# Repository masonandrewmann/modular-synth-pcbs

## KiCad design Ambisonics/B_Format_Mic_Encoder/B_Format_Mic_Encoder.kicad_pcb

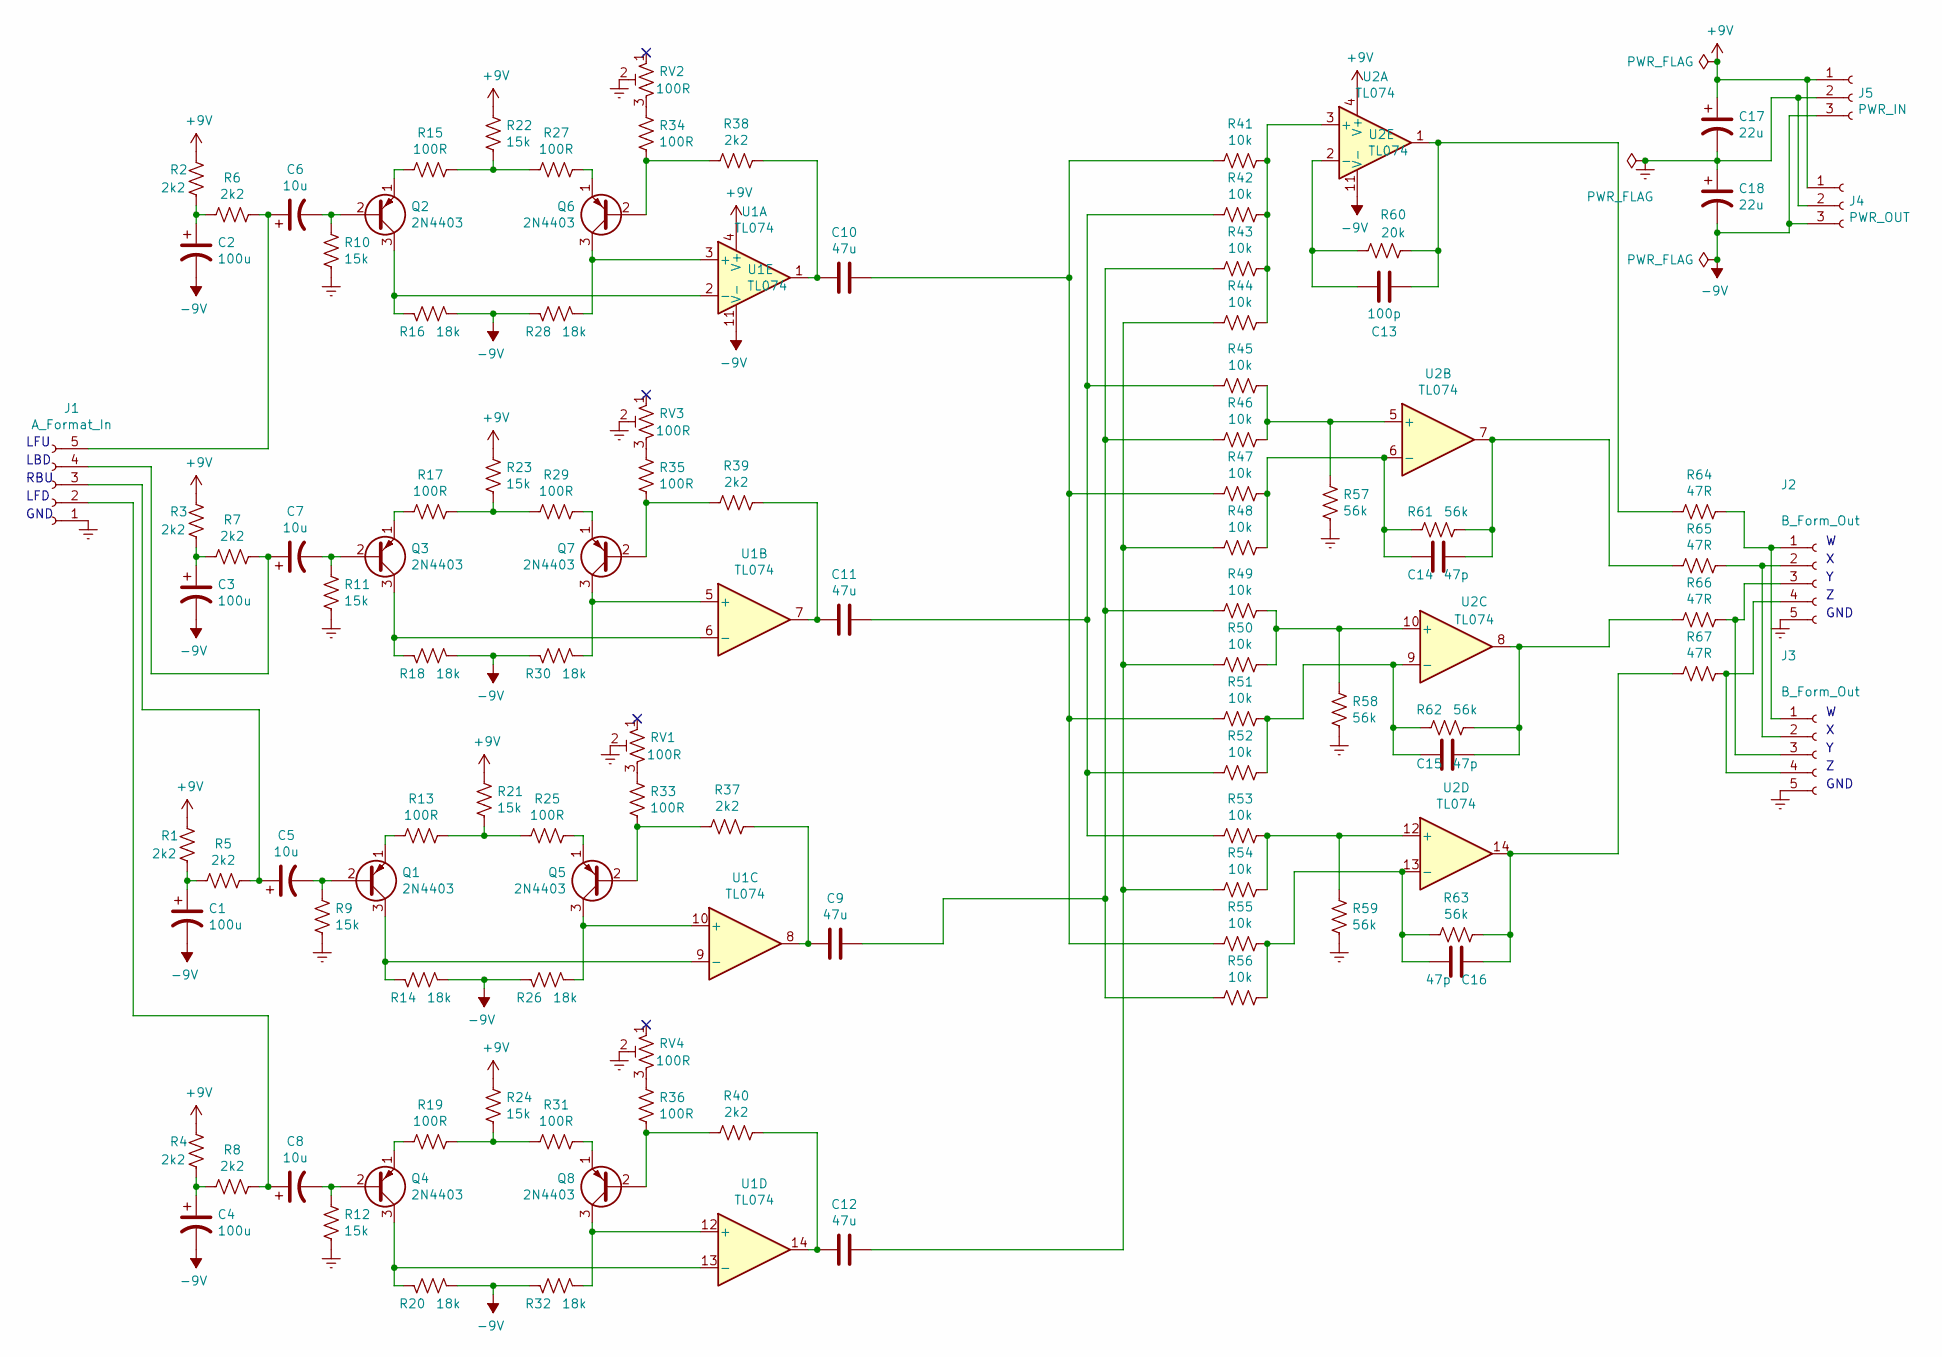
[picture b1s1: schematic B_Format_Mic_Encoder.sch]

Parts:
C1, C2, C3, C4: 100u; CP_Radial_D6.3mm_P2.50mm
C5, C6, C7, C8: 10u; CP_Radial_D6.3mm_P2.50mm
C9, C10, C11, C12: 47u; CP_Radial_D6.3mm_P2.50mm
C13: 100p; C_Rect_L7.0mm_W2.5mm_P5.00mm
C14, C15, C16: 47p; C_Rect_L7.0mm_W2.5mm_P5.00mm
C17, C18: 22u; CP_Radial_D6.3mm_P2.50mm
J1: A_Format_In; JST_XH_B5B-XH-A_1x05_P2.50mm_Vertical
J2, J3: B_Form_Out; JST_XH_B5B-XH-A_1x05_P2.50mm_Vertical
J4: PWR_OUT; JST_XH_B3B-XH-A_1x03_P2.50mm_Vertical
J5: PWR_IN; JST_XH_B3B-XH-A_1x03_P2.50mm_Vertical
Q1, Q2, Q3, Q4, Q5, Q6, Q7, Q8: 2N4403; TO-92L_Inline_Wide
R1, R2, R3, R4, R5, R6, R7, R8, R37, R38, R39, R40: 2k2; R_Axial_DIN0207_L6.3mm_D2.5mm_P7.62mm_Horizontal
R9, R10, R11, R12, R21, R22, R23, R24: 15k; R_Axial_DIN0207_L6.3mm_D2.5mm_P7.62mm_Horizontal
R13, R15, R17, R19, R25, R27, R29, R31, R33, R34, R35, R36: 100R; R_Axial_DIN0207_L6.3mm_D2.5mm_P7.62mm_Horizontal
R14, R16, R18, R20, R26, R28, R30, R32: 18k; R_Axial_DIN0207_L6.3mm_D2.5mm_P7.62mm_Horizontal
R41, R42, R43, R44, R45, R46, R47, R48, R49, R50, R51, R52, R53, R54, R55, R56: 10k; R_Axial_DIN0207_L6.3mm_D2.5mm_P7.62mm_Horizontal
R57, R58, R59, R61, R62, R63: 56k; R_Axial_DIN0207_L6.3mm_D2.5mm_P7.62mm_Horizontal
R60: 20k; R_Axial_DIN0207_L6.3mm_D2.5mm_P7.62mm_Horizontal
R64, R65, R66, R67: 47R; R_Axial_DIN0207_L6.3mm_D2.5mm_P7.62mm_Horizontal
RV1, RV2, RV3, RV4: 100R; Potentiometer_Runtron_RM-065_Vertical
U1, U2: TL074; DIP-14_W7.62mm_Socket

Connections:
+9V: C17.1, J4.1, J5.1, R1.2, R2.2, R3.2, R4.2, R21.2, R22.2, R23.2, R24.2, U1.4 (V+), U2.4 (V+)
-9V: C1.2, C2.2, C3.2, C4.2, C18.2, J4.3, J5.3, R14.1, R16.1, R18.1, R20.1, R26.2, R28.2, R30.2, R32.2, U1.11 (V-), U2.11 (V-)
Earth: C17.2, C18.1, J1.1, J2.5, J3.5, J4.2, J5.2, R9.2, R10.2, R11.2, R12.2, R57.1, R58.1, R59.1, RV1.2, RV2.2, RV3.2, RV4.2
unnamed: C1.1, R1.1, R5.2
unnamed: C2.1, R2.1, R6.2
unnamed: C3.1, R3.1, R7.2
unnamed: C4.1, R4.1, R8.2
unnamed: C5.1, J1.3, R5.1
unnamed: C5.2, Q1.2 (B), R9.1
unnamed: C6.1, J1.5, R6.1
unnamed: C6.2, Q2.2 (B), R10.1
unnamed: C7.1, J1.4, R7.1
unnamed: C7.2, Q3.2 (B), R11.1
unnamed: C8.1, J1.2, R8.1
unnamed: C8.2, Q4.2 (B), R12.1
unnamed: C9.1, R43.2, R46.2, R49.2, R56.2
unnamed: C9.2, R37.2, U1.8
unnamed: C10.1, R41.2, R47.2, R51.2, R55.2
unnamed: C10.2, R38.2, U1.1
unnamed: C11.1, R42.2, R45.2, R52.2, R53.2
unnamed: C11.2, R39.2, U1.7
unnamed: C12.1, R44.2, R48.2, R50.2, R54.2
unnamed: C12.2, R40.2, U1.14
unnamed: C13.1, R60.1, R64.1, U2.1
unnamed: C13.2, R60.2, U2.2 (-)
unnamed: C14.1, R61.1, R65.1, U2.7
unnamed: C14.2, R47.1, R48.1, R61.2, U2.6 (-)
unnamed: C15.1, R62.1, R66.1, U2.8
unnamed: C15.2, R51.1, R52.1, R62.2, U2.9 (-)
unnamed: C16.1, R63.1, R67.1, U2.14
unnamed: C16.2, R55.1, R56.1, R63.2, U2.13 (-)
unnamed: J2.1, J3.1, R64.2
unnamed: J2.2, J3.2, R65.2
unnamed: J2.3, J3.3, R66.2
unnamed: J2.4, J3.4, R67.2
unnamed: Q1.1 (E), R13.2
unnamed: Q1.3 (C), R14.2, U1.9 (-)
unnamed: Q2.1 (E), R15.2
unnamed: Q2.3 (C), R16.2, U1.2 (-)
unnamed: Q3.1 (E), R17.2
unnamed: Q3.3 (C), R18.2, U1.6 (-)
unnamed: Q4.1 (E), R19.2
unnamed: Q4.3 (C), R20.2, U1.13 (-)
unnamed: Q5.1 (E), R25.1
unnamed: Q5.2 (B), R33.1, R37.1
unnamed: Q5.3 (C), R26.1, U1.10 (+)
unnamed: Q6.1 (E), R27.1
unnamed: Q6.2 (B), R34.1, R38.1
unnamed: Q6.3 (C), R28.1, U1.3 (+)
unnamed: Q7.1 (E), R29.1
unnamed: Q7.2 (B), R35.1, R39.1
unnamed: Q7.3 (C), R30.1, U1.5 (+)
unnamed: Q8.1 (E), R31.1
unnamed: Q8.2 (B), R36.1, R40.1
unnamed: Q8.3 (C), R32.1, U1.12 (+)
unnamed: R13.1, R21.1, R25.2
unnamed: R15.1, R22.1, R27.2
unnamed: R17.1, R23.1, R29.2
unnamed: R19.1, R24.1, R31.2
unnamed: R33.2, RV1.3
unnamed: R34.2, RV2.3
unnamed: R35.2, RV3.3
unnamed: R36.2, RV4.3
unnamed: R41.1, R42.1, R43.1, R44.1, U2.3 (+)
unnamed: R45.1, R46.1, R57.2, U2.5 (+)
unnamed: R49.1, R50.1, R58.2, U2.10 (+)
unnamed: R53.1, R54.1, R59.2, U2.12 (+)

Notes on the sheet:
LFU
LBD
RBU
LFD
GND

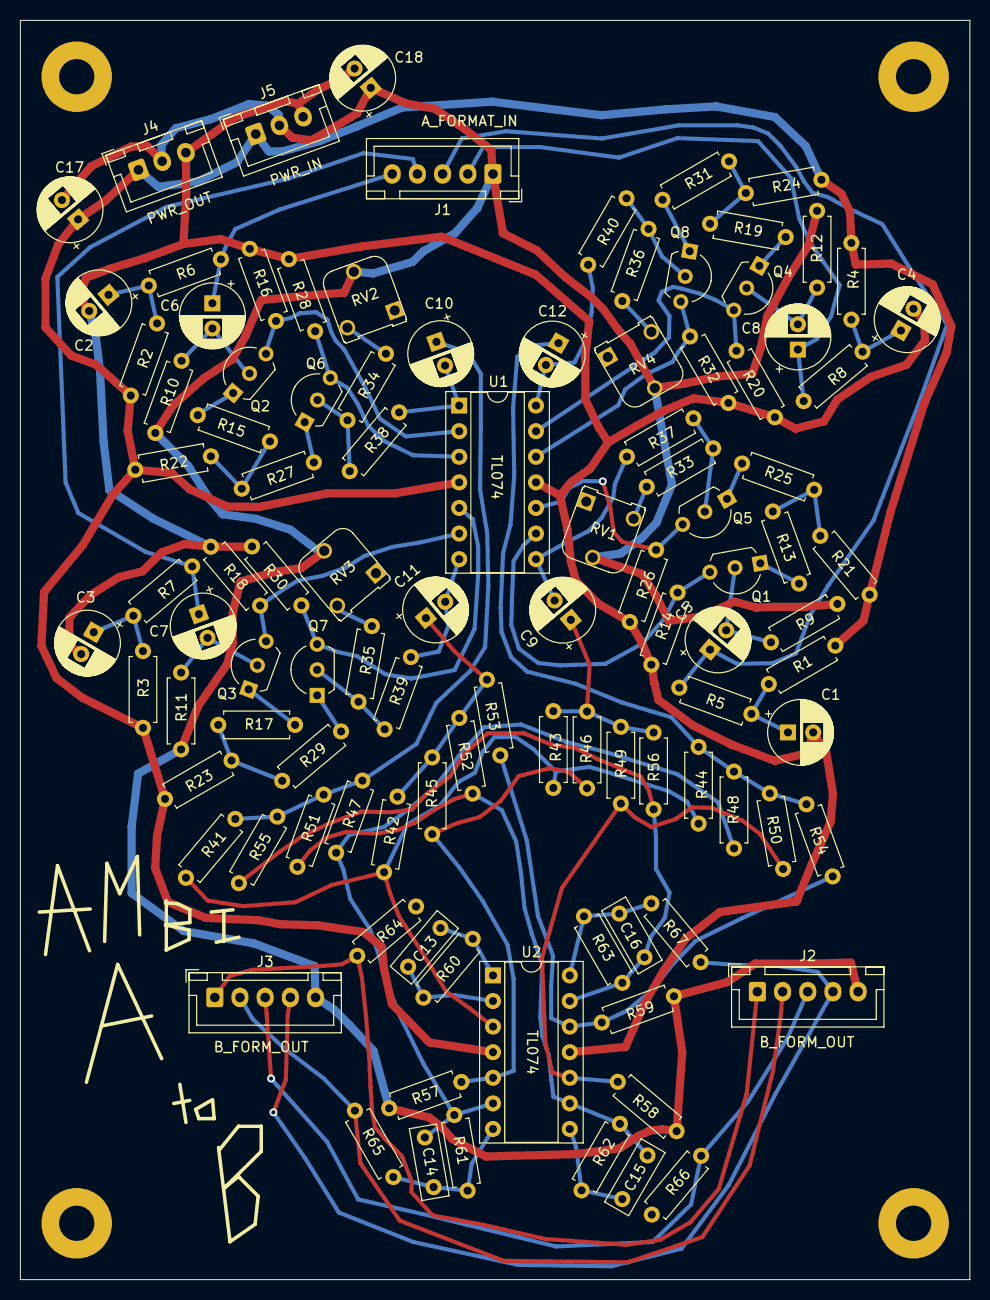
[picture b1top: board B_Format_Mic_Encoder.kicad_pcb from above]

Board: 2 copper layers, 94.2 x 125.0 mm, 104 parts (0 on the bottom side), 67 nets.

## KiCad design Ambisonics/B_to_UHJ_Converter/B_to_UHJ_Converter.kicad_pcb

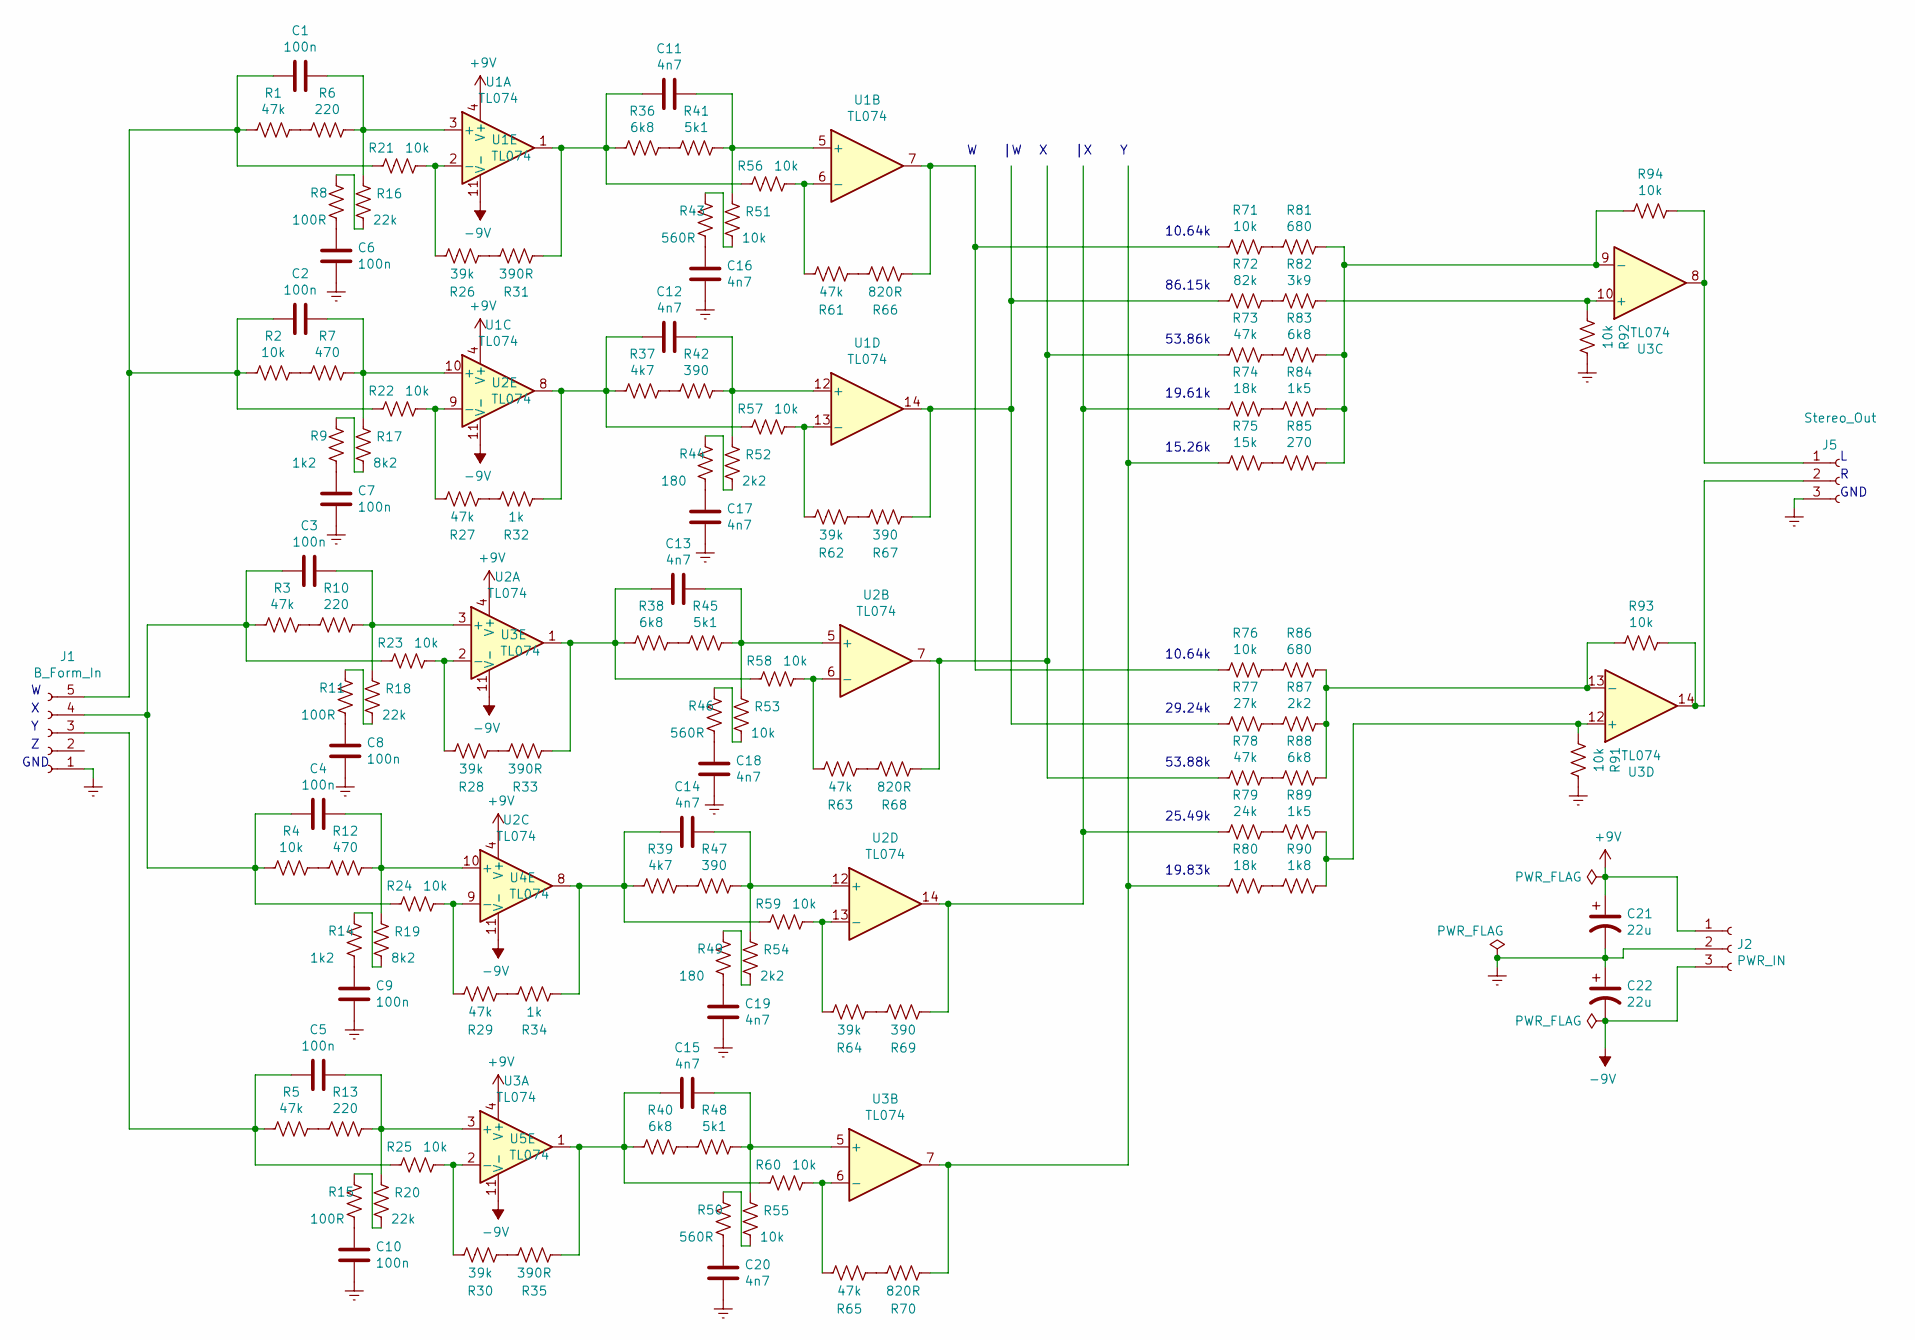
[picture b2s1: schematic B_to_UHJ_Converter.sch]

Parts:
C1, C2, C3, C4, C5, C6, C7, C8, C9, C10: 100n; C_Rect_L7.0mm_W2.5mm_P5.00mm
C11, C12, C13, C14, C15, C16, C17, C18, C19, C20: 4n7; C_Rect_L7.0mm_W2.5mm_P5.00mm
C21, C22: 22u; CP_Radial_D6.3mm_P2.50mm
J1: B_Form_In; JST_XH_B5B-XH-A_1x05_P2.50mm_Vertical
J2: PWR_IN; JST_XH_B3B-XH-A_1x03_P2.50mm_Vertical
J5: Stereo_Out; JST_XH_B3B-XH-A_1x03_P2.50mm_Vertical
R1, R3, R5, R27, R29, R61, R63, R65, R73, R78: 47k; R_Axial_DIN0207_L6.3mm_D2.5mm_P7.62mm_Horizontal
R2, R4, R21, R22, R23, R24, R25, R51, R53, R55, R56, R57, R58, R59, R60, R71, R76, R91, R92, R93, R94: 10k; R_Axial_DIN0207_L6.3mm_D2.5mm_P7.62mm_Horizontal
R6, R10, R13: 220; R_Axial_DIN0207_L6.3mm_D2.5mm_P7.62mm_Horizontal
R7, R12: 470; R_Axial_DIN0207_L6.3mm_D2.5mm_P7.62mm_Horizontal
R8, R11, R15: 100R; R_Axial_DIN0207_L6.3mm_D2.5mm_P7.62mm_Horizontal
R9, R14: 1k2; R_Axial_DIN0207_L6.3mm_D2.5mm_P7.62mm_Horizontal
R16, R18, R20: 22k; R_Axial_DIN0207_L6.3mm_D2.5mm_P7.62mm_Horizontal
R17, R19: 8k2; R_Axial_DIN0207_L6.3mm_D2.5mm_P7.62mm_Horizontal
R26, R28, R30, R62, R64: 39k; R_Axial_DIN0207_L6.3mm_D2.5mm_P7.62mm_Horizontal
R31, R33, R35: 390R; R_Axial_DIN0207_L6.3mm_D2.5mm_P7.62mm_Horizontal
R32, R34: 1k; R_Axial_DIN0207_L6.3mm_D2.5mm_P7.62mm_Horizontal
R36, R38, R40, R83, R88: 6k8; R_Axial_DIN0207_L6.3mm_D2.5mm_P7.62mm_Horizontal
R37, R39: 4k7; R_Axial_DIN0207_L6.3mm_D2.5mm_P7.62mm_Horizontal
R41, R45, R48: 5k1; R_Axial_DIN0207_L6.3mm_D2.5mm_P7.62mm_Horizontal
R42, R47, R67, R69: 390; R_Axial_DIN0207_L6.3mm_D2.5mm_P7.62mm_Horizontal
R43, R46, R50: 560R; R_Axial_DIN0207_L6.3mm_D2.5mm_P7.62mm_Horizontal
R44, R49: 180; R_Axial_DIN0207_L6.3mm_D2.5mm_P7.62mm_Horizontal
R52, R54, R87: 2k2; R_Axial_DIN0207_L6.3mm_D2.5mm_P7.62mm_Horizontal
R66, R68, R70: 820R; R_Axial_DIN0207_L6.3mm_D2.5mm_P7.62mm_Horizontal
R72: 82k; R_Axial_DIN0207_L6.3mm_D2.5mm_P7.62mm_Horizontal
R74, R80: 18k; R_Axial_DIN0207_L6.3mm_D2.5mm_P7.62mm_Horizontal
R75: 15k; R_Axial_DIN0207_L6.3mm_D2.5mm_P7.62mm_Horizontal
R77: 27k; R_Axial_DIN0207_L6.3mm_D2.5mm_P7.62mm_Horizontal
R79: 24k; R_Axial_DIN0207_L6.3mm_D2.5mm_P7.62mm_Horizontal
R81, R86: 680; R_Axial_DIN0207_L6.3mm_D2.5mm_P7.62mm_Horizontal
R82: 3k9; R_Axial_DIN0207_L6.3mm_D2.5mm_P7.62mm_Horizontal
R84, R89: 1k5; R_Axial_DIN0207_L6.3mm_D2.5mm_P7.62mm_Horizontal
R85: 270; R_Axial_DIN0207_L6.3mm_D2.5mm_P7.62mm_Horizontal
R90: 1k8; R_Axial_DIN0207_L6.3mm_D2.5mm_P7.62mm_Horizontal
U1, U2, U3, U4, U5: TL074; DIP-14_W7.62mm_Socket

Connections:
+9V: C21.1, J2.1, U1.4 (V+), U2.4 (V+), U3.4 (V+), U4.4 (V+), U5.4 (V+)
-9V: C22.2, J2.3, U1.11 (V-), U2.11 (V-), U3.11 (V-), U4.11 (V-), U5.11 (V-)
Earth: C6.1, C7.1, C8.1, C9.1, C10.1, C16.1, C17.1, C18.1, C19.1, C20.1, C21.2, C22.1, J1.1, J2.2, J5.3, R91.1, R92.1
unnamed: C1.1, R6.1, R16.2, U1.3 (+)
unnamed: C1.2, C2.2, J1.5, R1.2, R2.2, R21.2, R22.2
unnamed: C2.1, R7.1, R17.2, U1.10 (+)
unnamed: C3.1, R10.1, R18.2, U2.3 (+)
unnamed: C3.2, C4.2, J1.4, R3.2, R4.2, R23.2, R24.2
unnamed: C4.1, R12.1, R19.2, U2.10 (+)
unnamed: C5.1, R13.1, R20.2, U3.3 (+)
unnamed: C5.2, J1.3, R5.2, R25.2
unnamed: C6.2, R8.1
unnamed: C7.2, R9.1
unnamed: C8.2, R11.1
unnamed: C9.2, R14.1
unnamed: C10.2, R15.1
unnamed: C11.1, R41.1, R51.2, U1.5 (+)
unnamed: C11.2, R31.1, R36.2, R56.2, U1.1
unnamed: C12.1, R42.1, R52.2, U1.12 (+)
unnamed: C12.2, R32.1, R37.2, R57.2, U1.8
unnamed: C13.1, R45.1, R53.2, U2.5 (+)
unnamed: C13.2, R33.1, R38.2, R58.2, U2.1
unnamed: C14.1, R47.1, R54.2, U2.12 (+)
unnamed: C14.2, R34.1, R39.2, R59.2, U2.8
unnamed: C15.1, R48.1, R55.2, U3.5 (+)
unnamed: C15.2, R35.1, R40.2, R60.2, U3.1
unnamed: C16.2, R43.1
unnamed: C17.2, R44.1
unnamed: C18.2, R46.1
unnamed: C19.2, R49.1
unnamed: C20.2, R50.1
unnamed: J5.1, R94.1, U3.8
unnamed: J5.2, R93.1, U3.14
unnamed: R1.1, R6.2
unnamed: R2.1, R7.2
unnamed: R3.1, R10.2
unnamed: R11.2, R18.1
unnamed: R4.1, R12.2
unnamed: R5.1, R13.2
unnamed: R14.2, R19.1
unnamed: R15.2, R20.1
unnamed: R8.2, R16.1
unnamed: R9.2, R17.1
unnamed: R21.1, R26.2, U1.2 (-)
unnamed: R22.1, R27.2, U1.9 (-)
unnamed: R23.1, R28.2, U2.2 (-)
unnamed: R24.1, R29.2, U2.9 (-)
unnamed: R25.1, R30.2, U3.2 (-)
unnamed: R26.1, R31.2
unnamed: R27.1, R32.2
unnamed: R28.1, R33.2
unnamed: R29.1, R34.2
unnamed: R30.1, R35.2
unnamed: R36.1, R41.2
unnamed: R37.1, R42.2
unnamed: R38.1, R45.2
unnamed: R39.1, R47.2
unnamed: R40.1, R48.2
unnamed: R43.2, R51.1
unnamed: R44.2, R52.1
unnamed: R46.2, R53.1
unnamed: R49.2, R54.1
unnamed: R50.2, R55.1
unnamed: R56.1, R61.2, U1.6 (-)
unnamed: R57.1, R62.2, U1.13 (-)
unnamed: R58.1, R63.2, U2.6 (-)
unnamed: R59.1, R64.2, U2.13 (-)
unnamed: R60.1, R65.2, U3.6 (-)
unnamed: R61.1, R66.2
unnamed: R62.1, R67.2
unnamed: R63.1, R68.2
unnamed: R64.1, R69.2
unnamed: R65.1, R70.2
unnamed: R66.1, R71.2, R76.2, U1.7
unnamed: R67.1, R72.2, R77.2, U1.14
unnamed: R68.1, R73.2, R78.2, U2.7
unnamed: R69.1, R74.2, R79.2, U2.14
unnamed: R70.1, R75.2, R80.2, U3.7
unnamed: R71.1, R81.2
unnamed: R72.1, R82.2
unnamed: R73.1, R83.2
unnamed: R74.1, R84.2
unnamed: R75.1, R85.2
unnamed: R76.1, R86.2
unnamed: R77.1, R87.2
unnamed: R78.1, R88.2
unnamed: R79.1, R89.2
unnamed: R80.1, R90.2
unnamed: R81.1, R83.1, R84.1, R85.1, R94.2, U3.9 (-)
unnamed: R82.1, R92.2, U3.10 (+)
unnamed: R86.1, R87.1, R88.1, R93.2, U3.13 (-)
unnamed: R89.1, R90.1, R91.2, U3.12 (+)

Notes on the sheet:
10.64k
86.15k
53.86k
19.61k
15.26k
29.24k
53.88k
25.49k
19.83k
GND

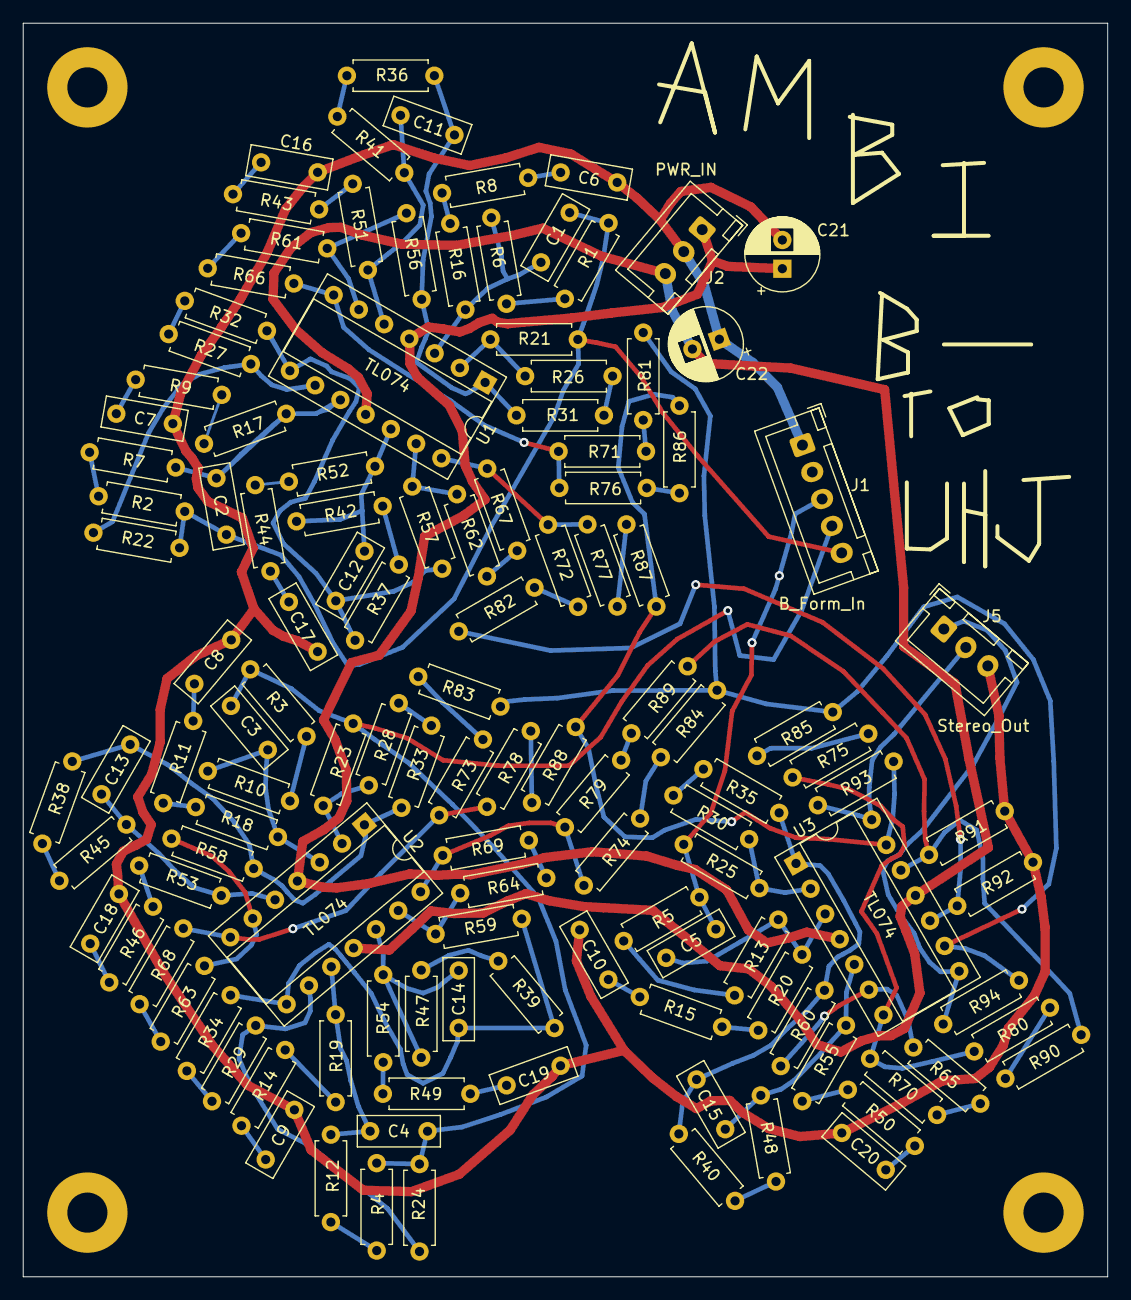
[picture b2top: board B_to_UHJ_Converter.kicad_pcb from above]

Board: 2 copper layers, 94.5 x 109.2 mm, 122 parts (0 on the bottom side), 92 nets.

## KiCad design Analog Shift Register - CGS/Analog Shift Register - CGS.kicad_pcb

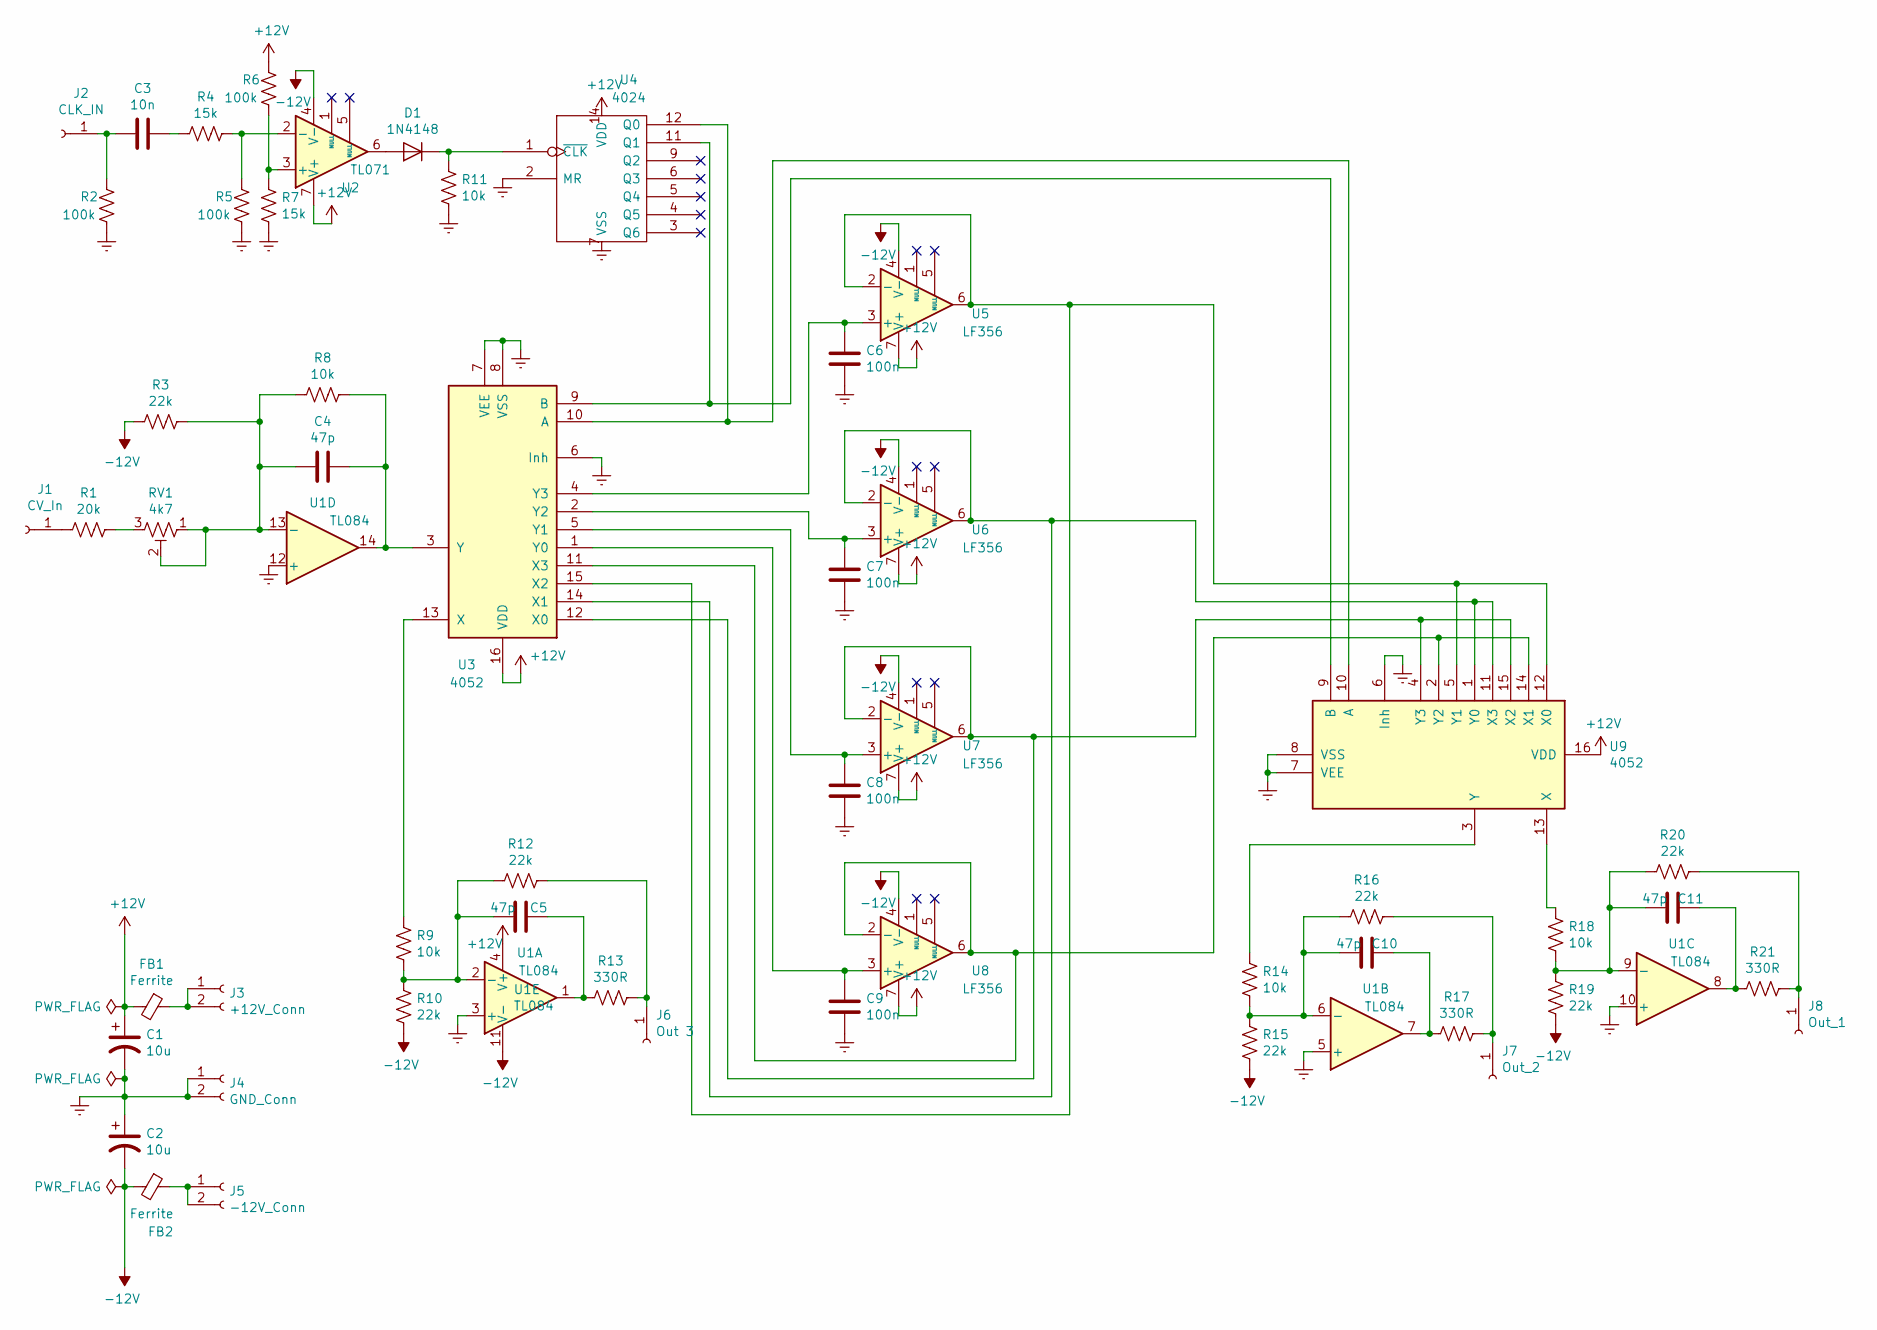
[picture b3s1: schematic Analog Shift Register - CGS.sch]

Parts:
C1, C2: 10u; CP_Radial_D4.0mm_P2.00mm
C3: 10n; C_Rect_L7.0mm_W2.5mm_P5.00mm
C4, C5, C10, C11: 47p; C_Rect_L7.0mm_W2.5mm_P5.00mm
C6, C7, C8, C9: 100n; C_Rect_L7.0mm_W2.5mm_P5.00mm
D1: 1N4148; D_T-1_P5.08mm_Horizontal
FB1, FB2: Ferrite; L_Axial_L7.0mm_D3.3mm_P10.16mm_Horizontal_Fastron_MICC
J1: CV_In; SolderWirePad_1x01_Drill1mm
J2: CLK_IN; SolderWirePad_1x01_Drill1mm
J3: +12V_Conn; SolderWirePad_1x02_P3.81mm_Drill1mm
J4: GND_Conn; SolderWirePad_1x02_P3.81mm_Drill1mm
J5: -12V_Conn; SolderWirePad_1x02_P3.81mm_Drill1mm
J6: Out 3; SolderWirePad_1x01_Drill1mm
J7: Out_2; SolderWirePad_1x01_Drill1mm
J8: Out_1; SolderWirePad_1x01_Drill1mm
R1: 20k; R_Axial_DIN0207_L6.3mm_D2.5mm_P7.62mm_Horizontal
R2, R5, R6: 100k; R_Axial_DIN0207_L6.3mm_D2.5mm_P7.62mm_Horizontal
R3, R10, R12, R15, R16, R19, R20: 22k; R_Axial_DIN0207_L6.3mm_D2.5mm_P7.62mm_Horizontal
R4, R7: 15k; R_Axial_DIN0207_L6.3mm_D2.5mm_P7.62mm_Horizontal
R8, R9, R11, R14, R18: 10k; R_Axial_DIN0207_L6.3mm_D2.5mm_P7.62mm_Horizontal
R13, R17, R21: 330R; R_Axial_DIN0207_L6.3mm_D2.5mm_P7.62mm_Horizontal
RV1: 4k7; Potentiometer_Runtron_RM-065_Vertical
U1: TL084; DIP-14_W7.62mm_Socket
U2: TL071; DIP-8_W7.62mm_Socket
U3, U9: 4052; DIP-16_W7.62mm_Socket
U4: 4024; DIP-14_W7.62mm_Socket
U5, U6, U7, U8: LF356; DIP-8_W7.62mm_Socket

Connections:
+12V: C1.1, FB1.2, R6.2, U1.4 (V+), U2.7 (V+), U3.16 (VDD), U4.14 (VDD), U5.7 (V+), U6.7 (V+), U7.7 (V+), U8.7 (V+), U9.16 (VDD)
-12V: C2.2, FB2.2, R3.2, R10.1, R15.1, R19.1, U1.11 (V-), U2.4 (V-), U5.4 (V-), U6.4 (V-), U7.4 (V-), U8.4 (V-)
Earth: C1.2, C2.1, C6.2, C7.2, C8.2, C9.2, J4.1, J4.2, R2.1, R5.1, R7.1, R11.1, U1.3 (+), U1.5 (+), U1.10 (+), U1.12 (+), U3.6 (Inh), U3.7 (VEE), U3.8 (VSS), U4.2 (MR), U4.7 (VSS), U9.6 (Inh), U9.7 (VEE), U9.8 (VSS)
unnamed: C3.1, R4.1
unnamed: C3.2, J2.1, R2.2
unnamed: C4.1, R8.1, U1.14, U3.3 (Y)
unnamed: C4.2, R3.1, R8.2, RV1.1, RV1.2, U1.13 (-)
unnamed: C5.1, R13.2, U1.1
unnamed: C5.2, R9.1, R10.2, R12.2, U1.2 (-)
unnamed: C6.1, U3.4 (Y3), U5.3 (+)
unnamed: C7.1, U3.2 (Y2), U6.3 (+)
unnamed: C8.1, U3.5 (Y1), U7.3 (+)
unnamed: C9.1, U3.1 (Y0), U8.3 (+)
unnamed: C10.1, R17.2, U1.7
unnamed: C10.2, R14.1, R15.2, R16.2, U1.6 (-)
unnamed: C11.1, R21.2, U1.8
unnamed: C11.2, R18.1, R19.2, R20.2, U1.9 (-)
unnamed: D1.1 (K), R11.2, U4.1 (~CLK)
unnamed: D1.2 (A), U2.6
unnamed: FB1.1, J3.1, J3.2
unnamed: FB2.1, J5.1, J5.2
unnamed: J1.1, R1.2
unnamed: J6.1, R12.1, R13.1
unnamed: J7.1, R16.1, R17.1
unnamed: J8.1, R20.1, R21.1
unnamed: R1.1, RV1.3
unnamed: R4.2, R5.2, U2.2 (-)
unnamed: R6.1, R7.2, U2.3 (+)
unnamed: R9.2, U3.13 (X)
unnamed: R14.2, U9.3 (Y)
unnamed: R18.2, U9.13 (X)
unnamed: U3.9 (B), U4.11 (Q1), U9.9 (B)
unnamed: U3.10 (A), U4.12 (Q0), U9.10 (A)
unnamed: U3.11 (X3), U8.2 (-), U8.6, U9.2 (Y2), U9.14 (X1)
unnamed: U3.12 (X0), U7.2 (-), U7.6, U9.4 (Y3), U9.15 (X2)
unnamed: U3.14 (X1), U6.2 (-), U6.6, U9.1 (Y0), U9.11 (X3)
unnamed: U3.15 (X2), U5.2 (-), U5.6, U9.5 (Y1), U9.12 (X0)

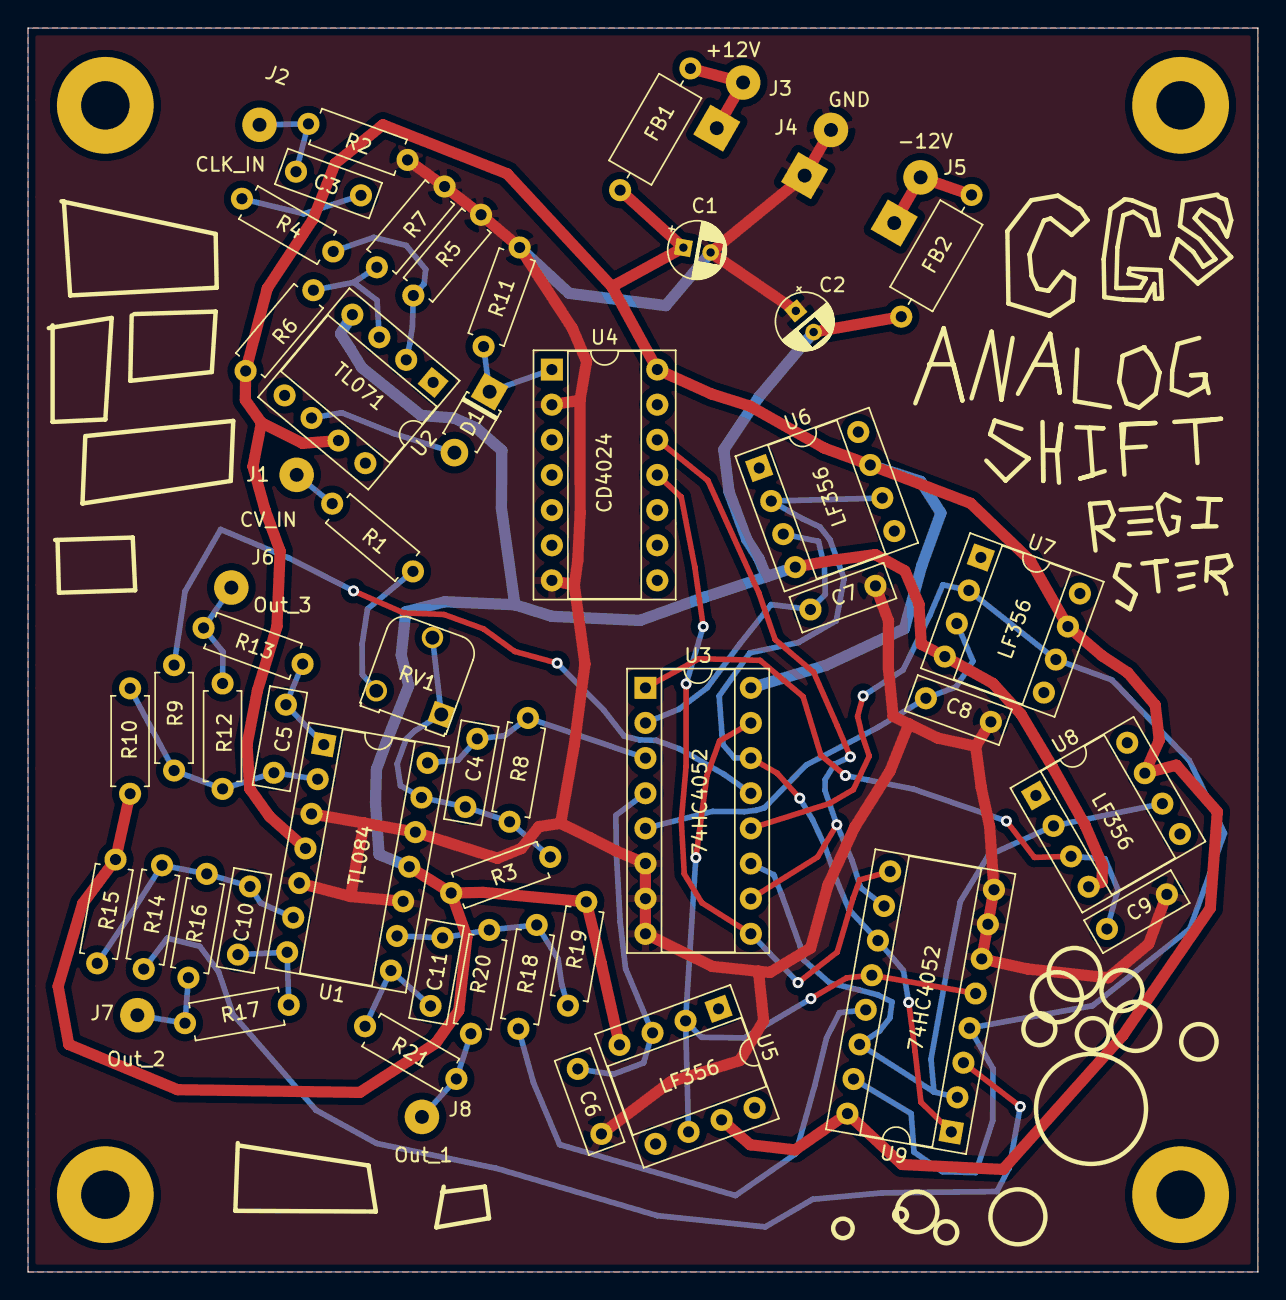
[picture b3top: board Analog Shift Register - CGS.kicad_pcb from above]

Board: 2 copper layers, 88.9 x 89.9 mm, 53 parts (0 on the bottom side), 37 nets.

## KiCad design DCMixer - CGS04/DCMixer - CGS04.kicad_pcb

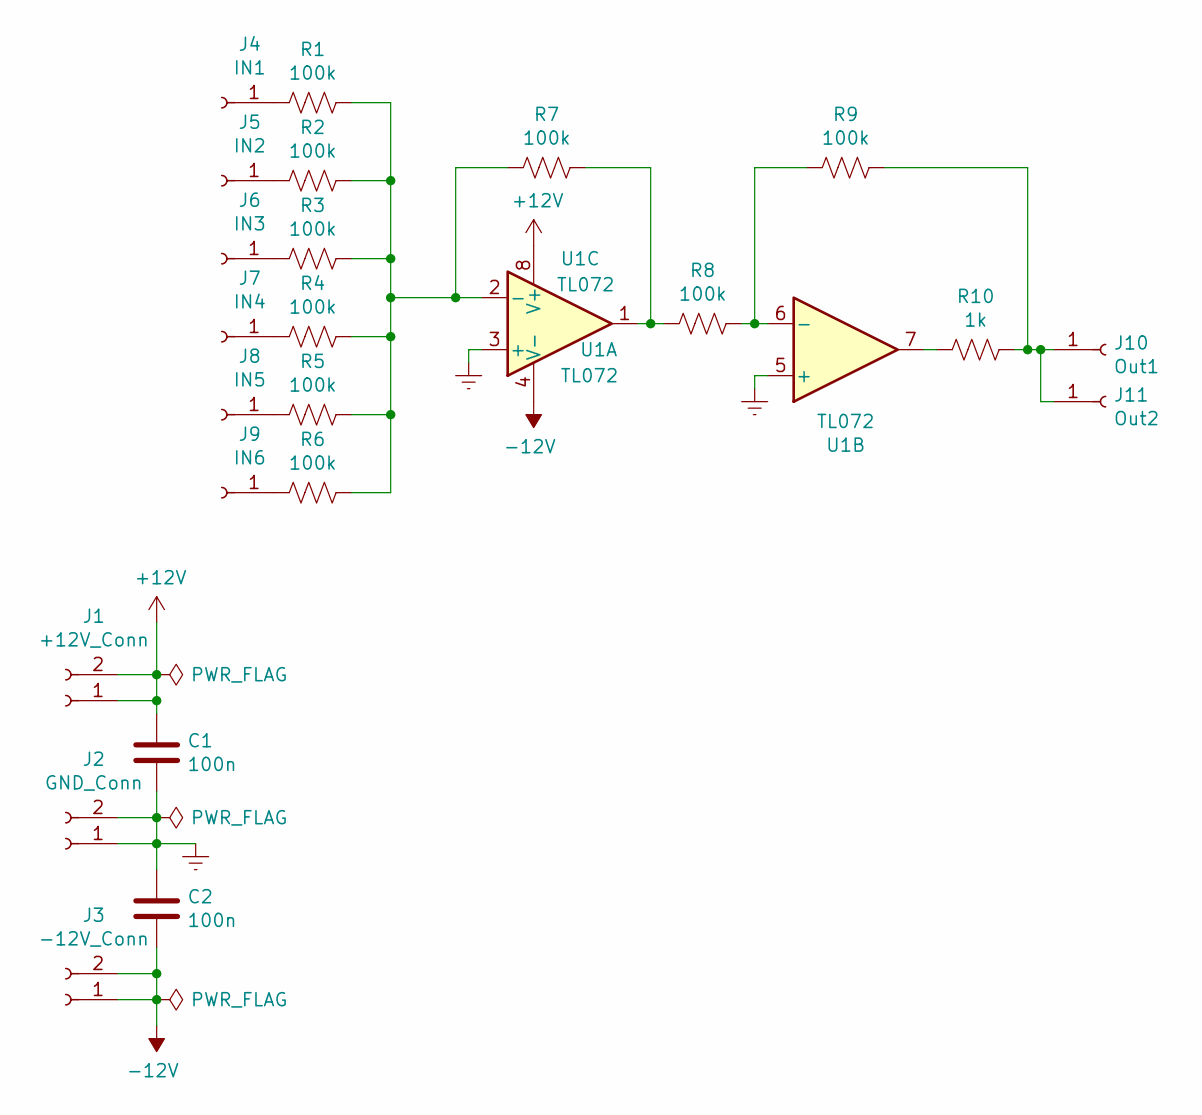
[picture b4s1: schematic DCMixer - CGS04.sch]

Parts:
C1, C2: 100n; C_Rect_L7.0mm_W2.5mm_P5.00mm
J1: +12V_Conn; SolderWirePad_1x02_P3.81mm_Drill1mm
J2: GND_Conn; SolderWirePad_1x02_P3.81mm_Drill1mm
J3: -12V_Conn; SolderWirePad_1x02_P3.81mm_Drill1mm
J4: IN1; SolderWirePad_1x01_Drill1mm
J5: IN2; SolderWirePad_1x01_Drill1mm
J6: IN3; SolderWirePad_1x01_Drill1mm
J7: IN4; SolderWirePad_1x01_Drill1mm
J8: IN5; SolderWirePad_1x01_Drill1mm
J9: IN6; SolderWirePad_1x01_Drill1mm
J10: Out1; SolderWirePad_1x01_Drill1mm
J11: Out2; SolderWirePad_1x01_Drill1mm
R1, R2, R3, R4, R5, R6, R7, R8, R9: 100k; R_Axial_DIN0207_L6.3mm_D2.5mm_P7.62mm_Horizontal
R10: 1k; R_Axial_DIN0207_L6.3mm_D2.5mm_P7.62mm_Horizontal
U1: TL072; DIP-8_W7.62mm_Socket

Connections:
+12V: C1.1, J1.1, J1.2, U1.8 (V+)
-12V: C2.2, J3.1, J3.2, U1.4 (V-)
Earth: C1.2, C2.1, J2.1, J2.2, U1.3 (+), U1.5 (+)
unnamed: J4.1, R1.2
unnamed: J5.1, R2.2
unnamed: J6.1, R3.2
unnamed: J7.1, R4.2
unnamed: J8.1, R5.2
unnamed: J9.1, R6.2
unnamed: J10.1, J11.1, R9.1, R10.1
unnamed: R1.1, R2.1, R3.1, R4.1, R5.1, R6.1, R7.2, U1.2 (-)
unnamed: R7.1, R8.2, U1.1
unnamed: R8.1, R9.2, U1.6 (-)
unnamed: R10.2, U1.7

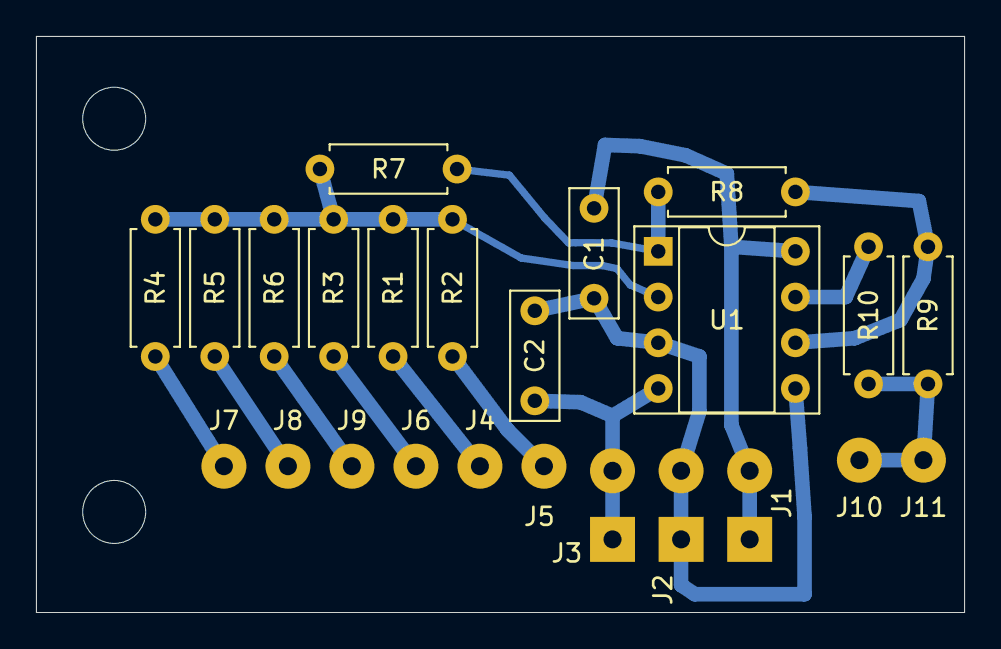
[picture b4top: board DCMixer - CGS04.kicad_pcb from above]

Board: 2 copper layers, 51.6 x 32.0 mm, 24 parts (0 on the bottom side), 14 nets.
